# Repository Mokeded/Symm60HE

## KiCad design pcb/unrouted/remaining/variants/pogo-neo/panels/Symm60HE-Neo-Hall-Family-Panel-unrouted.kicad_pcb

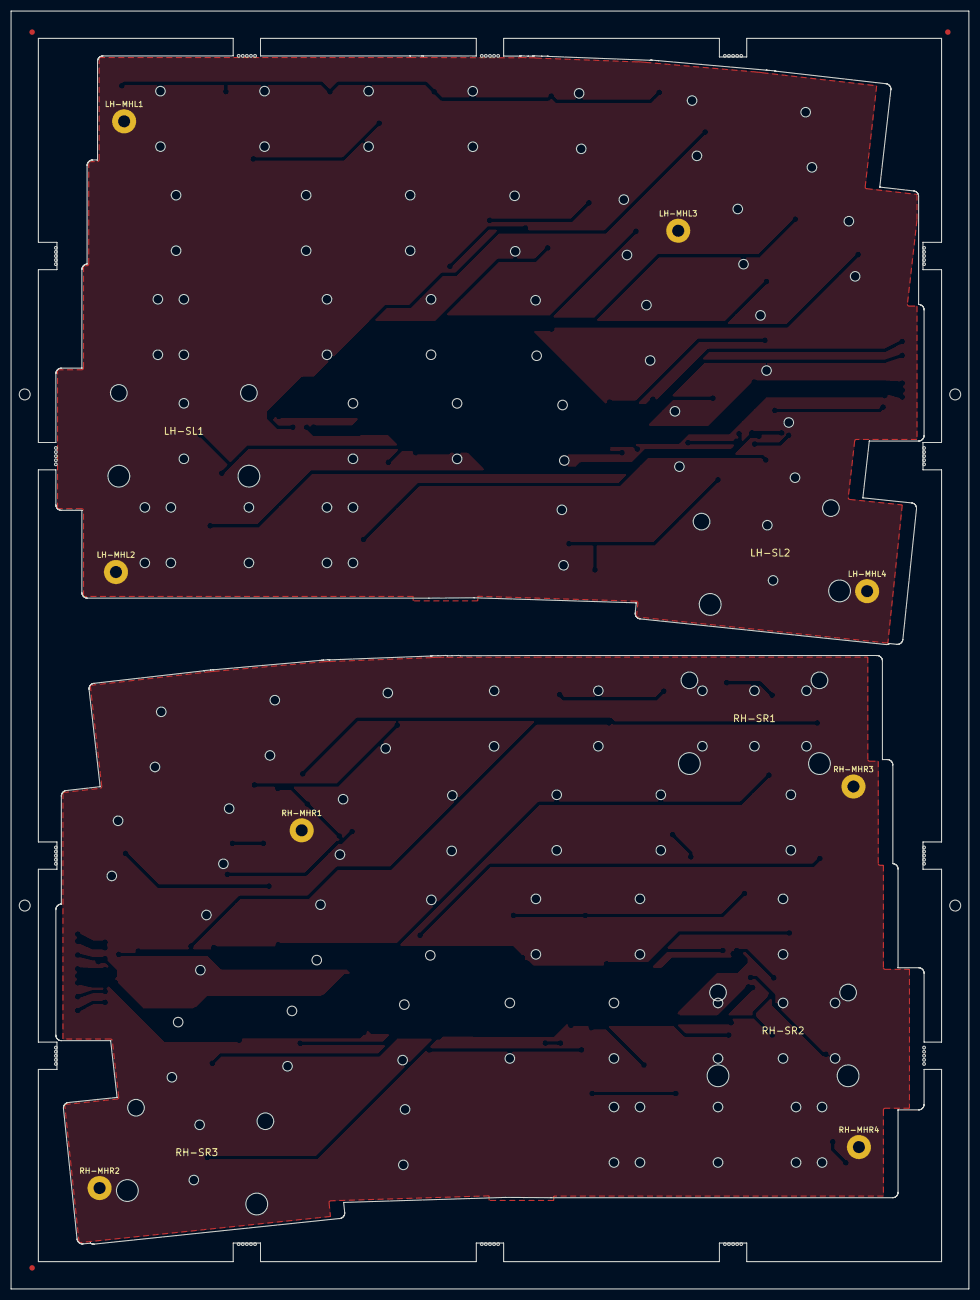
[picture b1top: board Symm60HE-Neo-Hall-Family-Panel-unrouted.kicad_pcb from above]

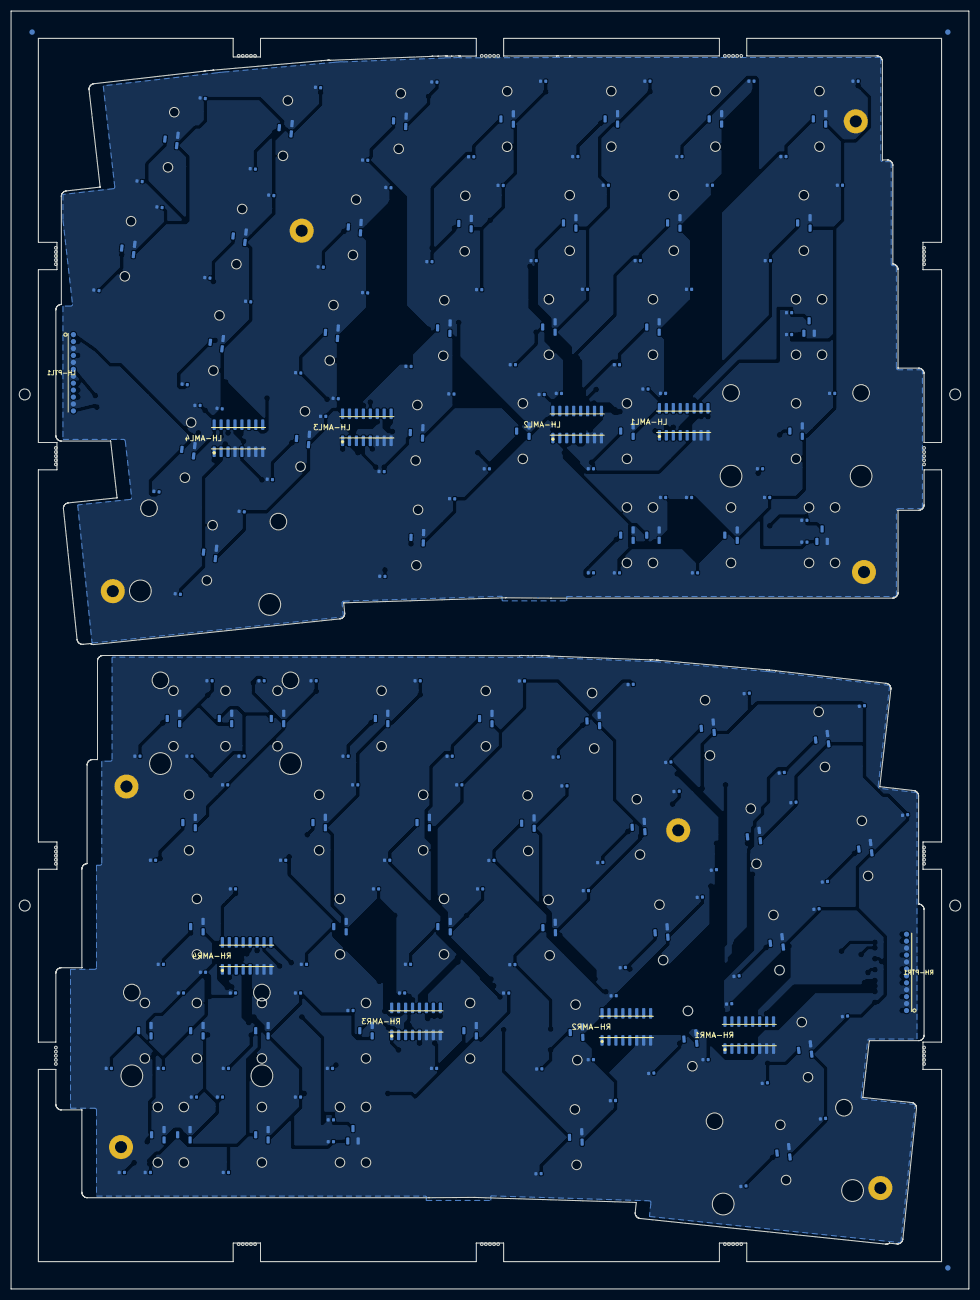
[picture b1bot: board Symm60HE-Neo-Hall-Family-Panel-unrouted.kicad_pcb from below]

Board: 2 copper layers, 175.3 x 233.9 mm, 318 parts (228 on the bottom side), 81 nets, no tracks yet.

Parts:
FIDB1, FIDB2, FIDB3: FIDUCIAL_1MM_BCU; Fiducial_1mm_BCu
FIDF1, FIDF2, FIDF3: FIDUCIAL_1MM_FCU; Fiducial_1mm_FCu
LH-AML1, LH-AML2, LH-AML3, LH-AML4: SN74LV4051A; AM1_SOIC-16_3.9x9.9mm_P1.27mm
LH-CL1A, LH-CL2A, LH-CL3A, LH-CL4A, LH-CL5A, LH-CL6A, LH-CL7A, LH-CL8A, LH-CL9A, LH-CL10A, LH-CL11A, LH-CL12A, LH-CL13A, LH-CL14A, LH-CL15A, LH-CL16A, LH-CL17A, LH-CL18A, LH-CL19A, LH-CL20A, LH-CL21A, LH-CL22A, LH-CL23A, LH-CL24A, LH-CL25A, LH-CL26A, LH-CL27A, LH-CL29A, LH-CL30A, LH-CL31A, LH-CL32A, LH-CL33A: 100n; C1_C_0402_1005Metric
LH-CL1B, LH-CL2B, LH-CL3B, LH-CL4B, LH-CL5B, LH-CL6B, LH-CL7B, LH-CL8B, LH-CL9B, LH-CL10B, LH-CL11B, LH-CL12B, LH-CL13B, LH-CL14B, LH-CL15B, LH-CL16B, LH-CL17B, LH-CL18B, LH-CL19B, LH-CL20B, LH-CL21B, LH-CL22B, LH-CL23B, LH-CL24B, LH-CL25B, LH-CL26B, LH-CL27B, LH-CL29B, LH-CL30B, LH-CL31B, LH-CL32B, LH-CL33B: 4.7n; C1_C_0402_1005Metric
LH-CML1, LH-CML2, LH-CML3, LH-CML4: 100n; C1_C_0402_1005Metric
LH-HEL1, LH-HEL2, LH-HEL3, LH-HEL4, LH-HEL5, LH-HEL6, LH-HEL7, LH-HEL9, LH-HEL10, LH-HEL11, LH-HEL12, LH-HEL13, LH-HEL14, LH-HEL16, LH-HEL17, LH-HEL18, LH-HEL19, LH-HEL20, LH-HEL22, LH-HEL23, LH-HEL24, LH-HEL25, LH-HEL26, LH-HEL29, LH-HEL31: MT9102ET; HE_KEY_1.00u
LH-HEL8, LH-HEL30, LH-HEL32: MT9102ET; HE_KEY_1.50u
LH-HEL15, LH-HEL27: MT9102ET; HE_SHARED_MIDPOINT
LH-HEL21, LH-HEL33: MT9102ET; HE_KEY_2.25u
LH-KML15N, LH-KML15S, LH-KML27A, LH-KML27N: MX_MECHANICAL_ONLY; HE_KEY_MECHANICAL_ONLY
LH-MHL1, LH-MHL2, LH-MHL3, LH-MHL4: M2; MountingHole_2.2mm_M2_Pad
LH-PTL1: 856-10-012-30-051000; MillMax_856-10-012-30-051000
LH-SL1, LH-SL2: STAB_MX; STABILIZER_MX_2U
MB1, MB2, MB3, MB4, MB5, MB6, MB7, MB8, MB9, MB10, MB11, MB12, MB13, MB14, MB15, MB16, MB17, MB18, MB19, MB20, MB21, MB22, MB23, MB24, MB25, MB26, MB27, MB28, MB29, MB30, MB31, MB32, MB33, MB34, MB35, MB36, MB37, MB38, MB39, MB40, MB41, MB42, MB43, MB44, MB45, MB46, MB47, MB48, MB49, MB50, MB51, MB52, MB53, MB54, MB55, MB56, MB57, MB58, MB59, MB60, MB61, MB62, MB63, MB64, MB65, MB66, MB67, MB68, MB69, MB70: MOUSE_BITE_0.5MM; MouseBite_0.5mm
RH-AMR1, RH-AMR2, RH-AMR3, RH-AMR4: SN74LV4051A; AM1_SOIC-16_3.9x9.9mm_P1.27mm
RH-CMR1, RH-CMR2, RH-CMR3, RH-CMR4: 100n; C1_C_0402_1005Metric
RH-CR1A, RH-CR2A, RH-CR3A, RH-CR4A, RH-CR5A, RH-CR6A, RH-CR7A, RH-CR8A, RH-CR9A, RH-CR10A, RH-CR11A, RH-CR12A, RH-CR13A, RH-CR14A, RH-CR15A, RH-CR16A, RH-CR17A, RH-CR18A, RH-CR19A, RH-CR20A, RH-CR21A, RH-CR22A, RH-CR23A, RH-CR24A, RH-CR25A, RH-CR26A, RH-CR27A, RH-CR28A, RH-CR29A, RH-CR30A, RH-CR32A, RH-CR33A, RH-CR34A, RH-CR35A, RH-CR36A: 100n; C1_C_0402_1005Metric
RH-CR1B, RH-CR2B, RH-CR3B, RH-CR4B, RH-CR5B, RH-CR6B, RH-CR7B, RH-CR8B, RH-CR9B, RH-CR10B, RH-CR11B, RH-CR12B, RH-CR13B, RH-CR14B, RH-CR15B, RH-CR16B, RH-CR17B, RH-CR18B, RH-CR19B, RH-CR20B, RH-CR21B, RH-CR22B, RH-CR23B, RH-CR24B, RH-CR25B, RH-CR26B, RH-CR27B, RH-CR28B, RH-CR29B, RH-CR30B, RH-CR32B, RH-CR33B, RH-CR34B, RH-CR35B, RH-CR36B: 4.7n; C1_C_0402_1005Metric
RH-HER1, RH-HER2, RH-HER3, RH-HER5, RH-HER6, RH-HER7, RH-HER8, RH-HER9, RH-HER10, RH-HER12, RH-HER13, RH-HER14, RH-HER15, RH-HER16, RH-HER17, RH-HER19, RH-HER20, RH-HER21, RH-HER22, RH-HER23, RH-HER24, RH-HER27, RH-HER28, RH-HER29, RH-HER32, RH-HER34: MT9102ET; HE_KEY_1.00u
RH-HER4: MT9102ET; HE_KEY_2.00u
RH-HER11, RH-HER33, RH-HER35: MT9102ET; HE_KEY_1.50u
RH-HER18: MT9102ET; HE_KEY_1.75u
RH-HER25, RH-HER36: MT9102ET; HE_KEY_2.25u
RH-HER26: MT9102ET; HE_KEY_1.25u
RH-HER30: MT9102ET; HE_SHARED_MIDPOINT
RH-KMR30A, RH-KMR30N: MX_MECHANICAL_ONLY; HE_KEY_MECHANICAL_ONLY
RH-MHR1, RH-MHR2, RH-MHR3, RH-MHR4: M2; MountingHole_2.2mm_M2_Pad
RH-PTR1: 856-10-012-30-051000; MillMax_856-10-012-30-051000
RH-SR1, RH-SR2, RH-SR3: STAB_MX; STABILIZER_MX_2U
TH1, TH2, TH3, TH4: TOOLING_HOLE_2MM; ToolingHole_2mm_NPTH

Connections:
/LH/+3V3A: LH-AML1.16, LH-AML2.16, LH-AML3.16, LH-AML4.16, LH-CL1A.1, LH-CL2A.1, LH-CL3A.1, LH-CL4A.1, LH-CL5A.1, LH-CL6A.1, LH-CL7A.1, LH-CL8A.1, LH-CL9A.1, LH-CL10A.1, LH-CL11A.1, LH-CL12A.1, LH-CL13A.1, LH-CL14A.1, LH-CL15A.1, LH-CL16A.1, LH-CL17A.1, LH-CL18A.1, LH-CL19A.1, LH-CL20A.1, LH-CL21A.1, LH-CL22A.1, LH-CL23A.1, LH-CL24A.1, LH-CL25A.1, LH-CL26A.1, LH-CL27A.1, LH-CL29A.1, LH-CL30A.1, LH-CL31A.1, LH-CL32A.1, LH-CL33A.1, LH-CML1.1, LH-CML2.1, LH-CML3.1, LH-CML4.1, LH-HEL1.1, LH-HEL2.1, LH-HEL3.1, LH-HEL4.1, LH-HEL5.1, LH-HEL6.1, LH-HEL7.1, LH-HEL8.1, LH-HEL9.1, LH-HEL10.1, LH-HEL11.1, LH-HEL12.1, LH-HEL13.1, LH-HEL14.1, LH-HEL15.1, LH-HEL16.1, LH-HEL17.1, LH-HEL18.1, LH-HEL19.1, LH-HEL20.1, LH-HEL21.1, LH-HEL22.1, LH-HEL23.1, LH-HEL24.1, LH-HEL25.1, LH-HEL26.1, LH-HEL27.1, LH-HEL29.1, LH-HEL30.1, LH-HEL31.1, LH-HEL32.1, LH-HEL33.1, LH-PTL1.12
/LH/ADC_L1: LH-AML1.3, LH-PTL1.6
/LH/ADC_L2: LH-AML2.3, LH-PTL1.4
/LH/ADC_L3: LH-AML3.3, LH-PTL1.2
/LH/ADC_L4: LH-AML4.3, LH-PTL1.1
/LH/GND: LH-AML1.6, LH-AML1.7, LH-AML1.8, LH-AML2.6, LH-AML2.7, LH-AML2.8, LH-AML3.6, LH-AML3.7, LH-AML3.8, LH-AML4.4, LH-AML4.6, LH-AML4.7, LH-AML4.8, LH-CL1A.2, LH-CL1B.2, LH-CL2A.2, LH-CL2B.2, LH-CL3A.2, LH-CL3B.2, LH-CL4A.2, LH-CL4B.2, LH-CL5A.2, LH-CL5B.2, LH-CL6A.2, LH-CL6B.2, LH-CL7A.2, LH-CL7B.2, LH-CL8A.2, LH-CL8B.2, LH-CL9A.2, LH-CL9B.2, LH-CL10A.2, LH-CL10B.2, LH-CL11A.2, LH-CL11B.2, LH-CL12A.2, LH-CL12B.2, LH-CL13A.2, LH-CL13B.2, LH-CL14A.2, LH-CL14B.2, LH-CL15A.2, LH-CL15B.2, LH-CL16A.2, LH-CL16B.2, LH-CL17A.2, LH-CL17B.2, LH-CL18A.2, LH-CL18B.2, LH-CL19A.2, LH-CL19B.2, LH-CL20A.2, LH-CL20B.2, LH-CL21A.2, LH-CL21B.2, LH-CL22A.2, LH-CL22B.2, LH-CL23A.2, LH-CL23B.2, LH-CL24A.2, LH-CL24B.2, LH-CL25A.2, LH-CL25B.2, LH-CL26A.2, LH-CL26B.2, LH-CL27A.2, LH-CL27B.2, LH-CL29A.2, LH-CL29B.2, LH-CL30A.2, LH-CL30B.2, LH-CL31A.2, LH-CL31B.2, LH-CL32A.2, LH-CL32B.2, LH-CL33A.2, LH-CL33B.2, LH-CML1.2, LH-CML2.2, LH-CML3.2, LH-CML4.2, LH-HEL1.2, LH-HEL2.2, LH-HEL3.2, LH-HEL4.2, LH-HEL5.2, LH-HEL6.2, LH-HEL7.2, LH-HEL8.2, LH-HEL9.2, LH-HEL10.2, LH-HEL11.2, LH-HEL12.2, LH-HEL13.2, LH-HEL14.2, LH-HEL15.2, LH-HEL16.2, LH-HEL17.2, LH-HEL18.2, LH-HEL19.2, LH-HEL20.2, LH-HEL21.2, LH-HEL22.2, LH-HEL23.2, LH-HEL24.2, LH-HEL25.2, LH-HEL26.2, LH-HEL27.2, LH-HEL29.2, LH-HEL30.2, LH-HEL31.2, LH-HEL32.2, LH-HEL33.2, LH-MHL1.1, LH-MHL2.1, LH-MHL3.1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
/LH/HE_L01: LH-AML1.13, LH-CL1B.1, LH-HEL1.3
/LH/HE_L02: LH-AML1.14, LH-CL2B.1, LH-HEL2.3
/LH/HE_L03: LH-AML1.15, LH-CL3B.1, LH-HEL3.3
/LH/HE_L04: LH-AML1.12, LH-CL4B.1, LH-HEL4.3
/LH/HE_L05: LH-AML1.1, LH-CL5B.1, LH-HEL5.3
/LH/HE_L06: LH-AML1.5, LH-CL6B.1, LH-HEL6.3
/LH/HE_L07: LH-AML1.2, LH-CL7B.1, LH-HEL7.3
/LH/HE_L08: LH-AML1.4, LH-CL8B.1, LH-HEL8.3
/LH/HE_L09: LH-AML2.13, LH-CL9B.1, LH-HEL9.3
/LH/HE_L10: LH-AML2.14, LH-CL10B.1, LH-HEL10.3
/LH/HE_L11: LH-AML2.15, LH-CL11B.1, LH-HEL11.3
/LH/HE_L12: LH-AML2.12, LH-CL12B.1, LH-HEL12.3
/LH/HE_L13: LH-AML2.1, LH-CL13B.1, LH-HEL13.3
/LH/HE_L14: LH-AML2.5, LH-CL14B.1, LH-HEL14.3
/LH/HE_L15: LH-AML2.2, LH-CL15B.1, LH-HEL15.3
/LH/HE_L16: LH-AML2.4, LH-CL16B.1, LH-HEL16.3
/LH/HE_L17: LH-AML3.13, LH-CL17B.1, LH-HEL17.3
/LH/HE_L18: LH-AML3.14, LH-CL18B.1, LH-HEL18.3
/LH/HE_L19: LH-AML3.15, LH-CL19B.1, LH-HEL19.3
/LH/HE_L20: LH-AML3.12, LH-CL20B.1, LH-HEL20.3
/LH/HE_L21: LH-AML3.1, LH-CL21B.1, LH-HEL21.3
/LH/HE_L22: LH-AML3.5, LH-CL22B.1, LH-HEL22.3
/LH/HE_L23: LH-AML3.2, LH-CL23B.1, LH-HEL23.3
/LH/HE_L24: LH-AML3.4, LH-CL24B.1, LH-HEL24.3
/LH/HE_L25: LH-AML4.13, LH-CL25B.1, LH-HEL25.3
/LH/HE_L26: LH-AML4.14, LH-CL26B.1, LH-HEL26.3
/LH/HE_L27: LH-AML4.15, LH-CL27B.1, LH-HEL27.3
/LH/HE_L28: LH-AML4.12, LH-CL29B.1, LH-CL30B.1, LH-HEL29.3, LH-HEL30.3
/LH/HE_L29: LH-AML4.1, LH-CL31B.1, LH-HEL31.3
/LH/HE_L30: LH-AML4.5, LH-CL32B.1, LH-HEL32.3
/LH/HE_L31: LH-AML4.2, LH-CL33B.1, LH-HEL33.3
/LH/MUX_A0: LH-AML1.11, LH-AML2.11, LH-AML3.11, LH-AML4.11, LH-PTL1.10
/LH/MUX_A1: LH-AML1.10, LH-AML2.10, LH-AML3.10, LH-AML4.10, LH-PTL1.9
/LH/MUX_A2: LH-AML1.9, LH-AML2.9, LH-AML3.9, LH-AML4.9, LH-PTL1.8
/RH/+3V3A: RH-AMR1.16, RH-AMR2.16, RH-AMR3.16, RH-AMR4.16, RH-CMR1.1, RH-CMR2.1, RH-CMR3.1, RH-CMR4.1, RH-CR1A.1, RH-CR2A.1, RH-CR3A.1, RH-CR4A.1, RH-CR5A.1, RH-CR6A.1, RH-CR7A.1, RH-CR8A.1, RH-CR9A.1, RH-CR10A.1, RH-CR11A.1, RH-CR12A.1, RH-CR13A.1, RH-CR14A.1, RH-CR15A.1, RH-CR16A.1, RH-CR17A.1, RH-CR18A.1, RH-CR19A.1, RH-CR20A.1, RH-CR21A.1, RH-CR22A.1, RH-CR23A.1, RH-CR24A.1, RH-CR25A.1, RH-CR26A.1, RH-CR27A.1, RH-CR28A.1, RH-CR29A.1, RH-CR30A.1, RH-CR32A.1, RH-CR33A.1, RH-CR34A.1, RH-CR35A.1, RH-CR36A.1, RH-HER1.1, RH-HER2.1, RH-HER3.1, RH-HER4.1, RH-HER5.1, RH-HER6.1, RH-HER7.1, RH-HER8.1, RH-HER9.1, RH-HER10.1, RH-HER11.1, RH-HER12.1, RH-HER13.1, RH-HER14.1, RH-HER15.1, RH-HER16.1, RH-HER17.1, RH-HER18.1, RH-HER19.1, RH-HER20.1, RH-HER21.1, RH-HER22.1, RH-HER23.1, RH-HER24.1, RH-HER25.1, RH-HER26.1, RH-HER27.1, RH-HER28.1, RH-HER29.1, RH-HER30.1, RH-HER32.1, RH-HER33.1, RH-HER34.1, RH-HER35.1, RH-HER36.1, RH-PTR1.1
/RH/ADC_R1: RH-AMR1.3, RH-PTR1.7
/RH/ADC_R2: RH-AMR2.3, RH-PTR1.9
/RH/ADC_R3: RH-AMR3.3, RH-PTR1.11
/RH/ADC_R4: RH-AMR4.3, RH-PTR1.12
/RH/GND: RH-AMR1.6, RH-AMR1.7, RH-AMR1.8, RH-AMR2.6, RH-AMR2.7, RH-AMR2.8, RH-AMR3.6, RH-AMR3.7, RH-AMR3.8, RH-AMR4.6, RH-AMR4.7, RH-AMR4.8, RH-CMR1.2, RH-CMR2.2, RH-CMR3.2, RH-CMR4.2, RH-CR1A.2, RH-CR1B.2, RH-CR2A.2, RH-CR2B.2, RH-CR3A.2, RH-CR3B.2, RH-CR4A.2, RH-CR4B.2, RH-CR5A.2, RH-CR5B.2, RH-CR6A.2, RH-CR6B.2, RH-CR7A.2, RH-CR7B.2, RH-CR8A.2, RH-CR8B.2, RH-CR9A.2, RH-CR9B.2, RH-CR10A.2, RH-CR10B.2, RH-CR11A.2, RH-CR11B.2, RH-CR12A.2, RH-CR12B.2, RH-CR13A.2, RH-CR13B.2, RH-CR14A.2, RH-CR14B.2, RH-CR15A.2, RH-CR15B.2, RH-CR16A.2, RH-CR16B.2, RH-CR17A.2, RH-CR17B.2, RH-CR18A.2, RH-CR18B.2, RH-CR19A.2, RH-CR19B.2, RH-CR20A.2, RH-CR20B.2, RH-CR21A.2, RH-CR21B.2, RH-CR22A.2, RH-CR22B.2, RH-CR23A.2, RH-CR23B.2, RH-CR24A.2, RH-CR24B.2, RH-CR25A.2, RH-CR25B.2, RH-CR26A.2, RH-CR26B.2, RH-CR27A.2, RH-CR27B.2, RH-CR28A.2, RH-CR28B.2, RH-CR29A.2, RH-CR29B.2, RH-CR30A.2, RH-CR30B.2, RH-CR32A.2, RH-CR32B.2, RH-CR33A.2, RH-CR33B.2, RH-CR34A.2, RH-CR34B.2, RH-CR35A.2, RH-CR35B.2, RH-CR36A.2, RH-CR36B.2, RH-HER1.2, RH-HER2.2, RH-HER3.2, RH-HER4.2, RH-HER5.2, RH-HER6.2, RH-HER7.2, RH-HER8.2, RH-HER9.2, RH-HER10.2, RH-HER11.2, RH-HER12.2, RH-HER13.2, RH-HER14.2, RH-HER15.2, RH-HER16.2, RH-HER17.2, RH-HER18.2, RH-HER19.2, RH-HER20.2, RH-HER21.2, RH-HER22.2, RH-HER23.2, RH-HER24.2, RH-HER25.2, RH-HER26.2, RH-HER27.2, RH-HER28.2, RH-HER29.2, RH-HER30.2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
/RH/HE_R01: RH-AMR1.13, RH-CR6B.1, RH-HER6.3
/RH/HE_R02: RH-AMR1.14, RH-CR1B.1, RH-HER1.3
/RH/HE_R03: RH-AMR1.15, RH-CR2B.1, RH-HER2.3
/RH/HE_R04: RH-AMR1.12, RH-CR3B.1, RH-CR4B.1, RH-HER3.3, RH-HER4.3
/RH/HE_R05: RH-AMR1.1, RH-CR5B.1, RH-HER5.3
/RH/HE_R06: RH-AMR1.5, RH-CR7B.1, RH-HER7.3
/RH/HE_R07: RH-AMR1.2, RH-CR8B.1, RH-HER8.3
/RH/HE_R08: RH-AMR1.4, RH-CR13B.1, RH-HER13.3
/RH/HE_R09: RH-AMR2.13, RH-CR12B.1, RH-HER12.3
/RH/HE_R10: RH-AMR2.14, RH-CR9B.1, RH-HER9.3
/RH/HE_R11: RH-AMR2.15, RH-CR10B.1, RH-HER10.3
/RH/HE_R12: RH-AMR2.12, RH-CR11B.1, RH-HER11.3
/RH/HE_R13: RH-AMR2.1, RH-CR14B.1, RH-HER14.3
/RH/HE_R14: RH-AMR2.5, RH-CR15B.1, RH-HER15.3
/RH/HE_R15: RH-AMR2.2, RH-CR19B.1, RH-HER19.3
/RH/HE_R16: RH-AMR2.4, RH-CR16B.1, RH-HER16.3
/RH/HE_R17: RH-AMR3.13, RH-CR17B.1, RH-HER17.3
/RH/HE_R18: RH-AMR3.14, RH-CR18B.1, RH-HER18.3
/RH/HE_R19: RH-AMR3.15, RH-CR20B.1, RH-HER20.3
/RH/HE_R20: RH-AMR3.12, RH-CR21B.1, RH-HER21.3
/RH/HE_R21: RH-AMR3.1, RH-CR27B.1, RH-HER27.3
/RH/HE_R22: RH-AMR3.5, RH-CR22B.1, RH-HER22.3
/RH/HE_R23: RH-AMR3.2, RH-CR23B.1, RH-HER23.3
/RH/HE_R24: RH-AMR3.4, RH-CR24B.1, RH-HER24.3
/RH/HE_R25: RH-AMR4.13, RH-CR25B.1, RH-CR26B.1, RH-HER25.3, RH-HER26.3
/RH/HE_R26: RH-AMR4.14, RH-CR28B.1, RH-HER28.3
/RH/HE_R27: RH-AMR4.15, RH-CR29B.1, RH-HER29.3
/RH/HE_R28: RH-AMR4.12, RH-CR35B.1, RH-HER35.3
/RH/HE_R29: RH-AMR4.1, RH-CR30B.1, RH-HER30.3
/RH/HE_R30: RH-AMR4.5, RH-CR32B.1, RH-CR33B.1, RH-HER32.3, RH-HER33.3
/RH/HE_R31: RH-AMR4.2, RH-CR34B.1, RH-HER34.3
/RH/HE_R32: RH-AMR4.4, RH-CR36B.1, RH-HER36.3
/RH/MUX_A0: RH-AMR1.11, RH-AMR2.11, RH-AMR3.11, RH-AMR4.11, RH-PTR1.3
/RH/MUX_A1: RH-AMR1.10, RH-AMR2.10, RH-AMR3.10, RH-AMR4.10, RH-PTR1.5
/RH/MUX_A2: RH-AMR1.9, RH-AMR2.9, RH-AMR3.9, RH-AMR4.9, RH-PTR1.6

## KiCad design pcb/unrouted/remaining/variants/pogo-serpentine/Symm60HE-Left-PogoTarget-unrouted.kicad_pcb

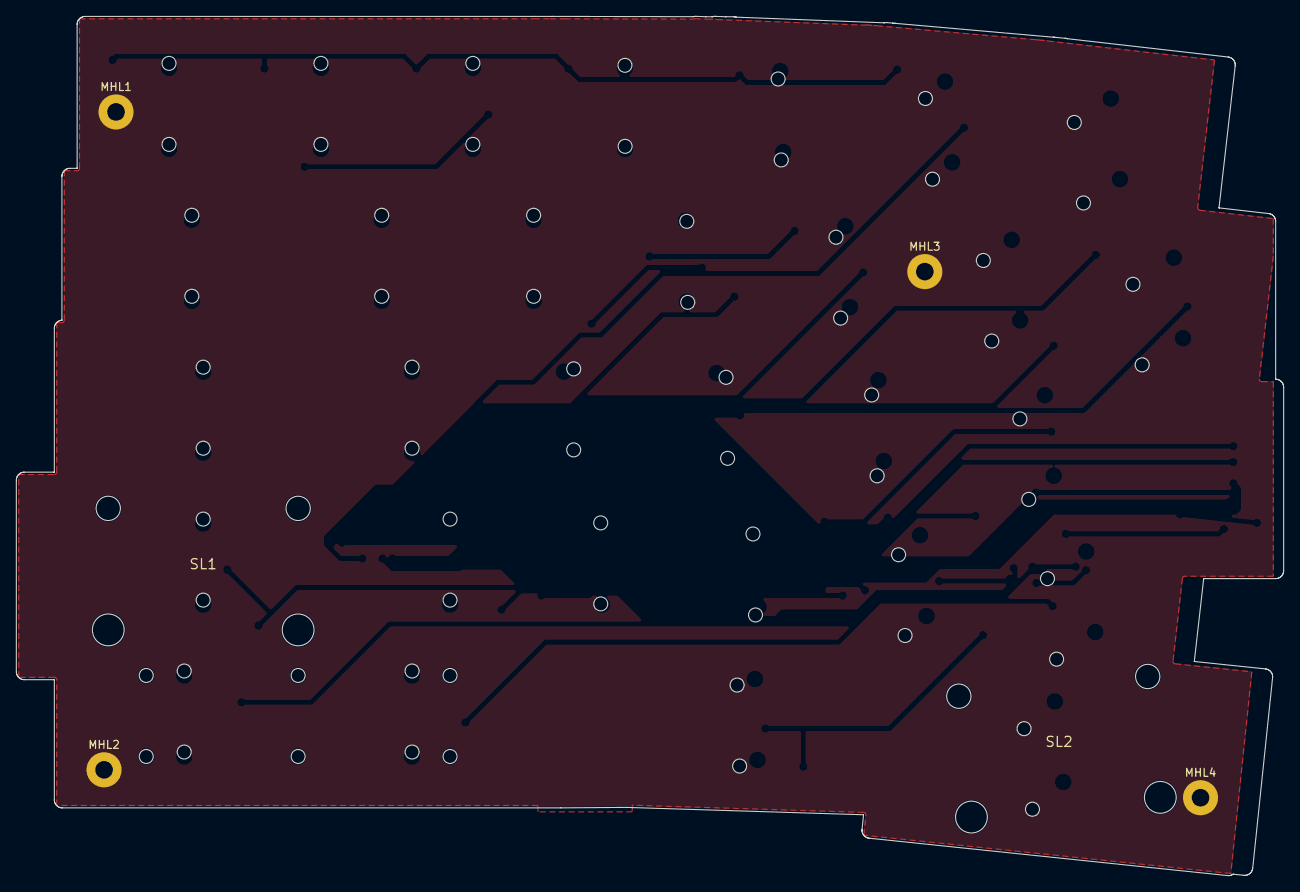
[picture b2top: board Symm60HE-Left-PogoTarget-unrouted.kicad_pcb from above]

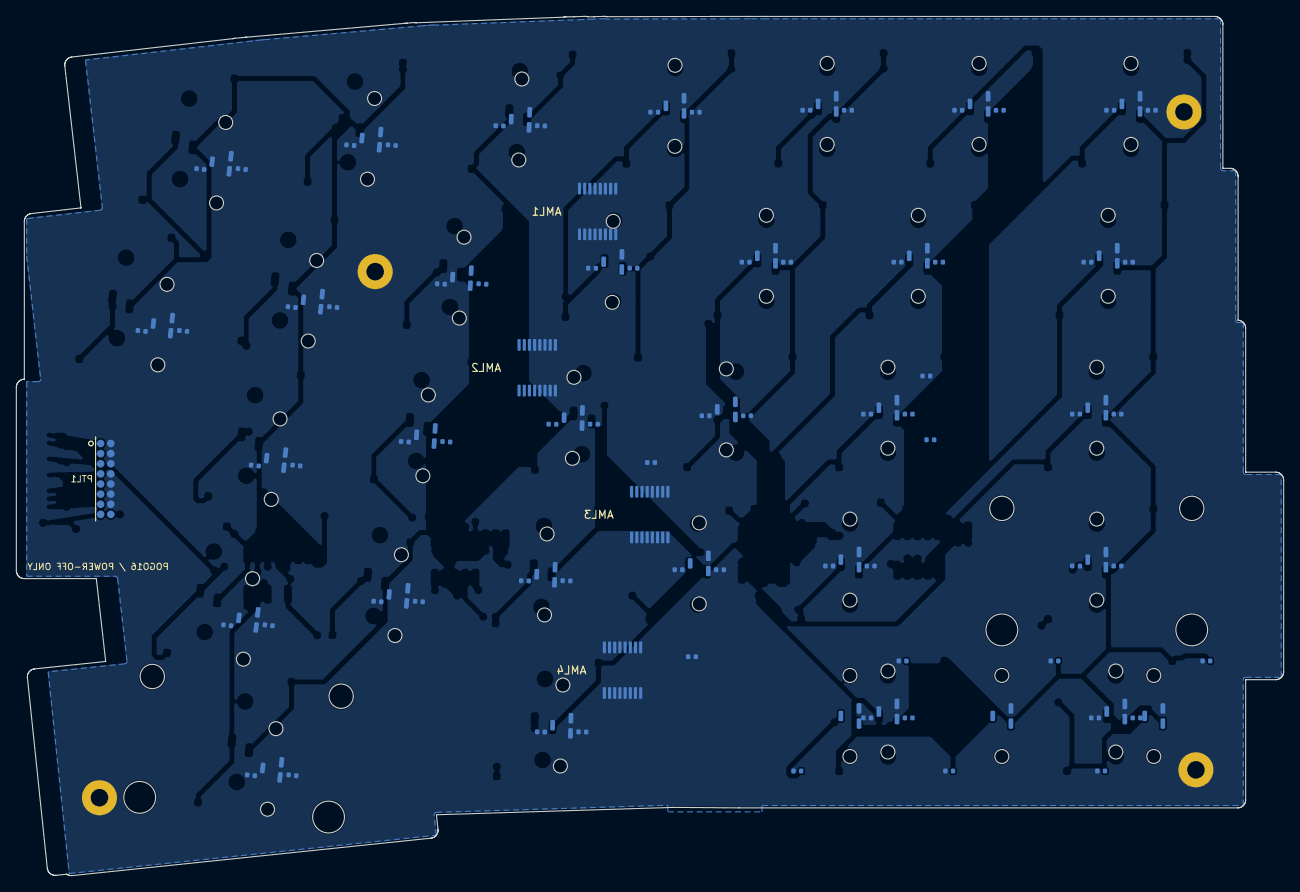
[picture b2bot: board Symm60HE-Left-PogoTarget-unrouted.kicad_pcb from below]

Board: 2 copper layers, 158.9 x 107.8 mm, 114 parts (108 on the bottom side), 40 nets, no tracks yet.

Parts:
AML1, AML2, AML3, AML4: SN74LV4051A; AM1_TSSOP-16_4.4x5mm_P0.65mm
CL1A, CL2A, CL3A, CL4A, CL5A, CL6A, CL7A, CL8A, CL9A, CL10A, CL11A, CL12A, CL13A, CL14A, CL15A, CL16A, CL17A, CL18A, CL19A, CL20A, CL21A, CL22A, CL23A, CL24A, CL25A, CL26A, CL27A, CL28A, CL29A, CL30A, CL31A, CL32A, CL33A: 100n; C1_C_0402_1005Metric
CL1B, CL2B, CL3B, CL4B, CL5B, CL6B, CL7B, CL8B, CL9B, CL10B, CL11B, CL12B, CL13B, CL14B, CL15B, CL16B, CL17B, CL18B, CL19B, CL20B, CL21B, CL22B, CL23B, CL24B, CL25B, CL26B, CL27B, CL28B, CL29B, CL30B, CL31B, CL32B, CL33B: 4.7n; C1_C_0402_1005Metric
CML1, CML2, CML3, CML4: 100n; C1_C_0402_1005Metric
HEL1, HEL2, HEL3, HEL4, HEL5, HEL6, HEL7, HEL9, HEL10, HEL11, HEL12, HEL13, HEL14, HEL16, HEL17, HEL18, HEL19, HEL20, HEL22, HEL23, HEL24, HEL25, HEL26, HEL27, HEL29, HEL31: MT9102ET; HE_KEY_1.00u
HEL8, HEL28, HEL30, HEL32: MT9102ET; HE_KEY_1.50u
HEL15: MT9102ET; HE_KEY_1.75u
HEL21, HEL33: MT9102ET; HE_KEY_2.25u
MHL1, MHL2, MHL3, MHL4: M2; MountingHole_2.2mm_M2_Pad
PTL1: 857-10-016-30-051000; MillMax_857-10-016-30-051000
SL1, SL2: STAB_MX; STABILIZER_MX_2U

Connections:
+3V3A: AML1.16, AML2.16, AML3.16, AML4.16, CL1A.1, CL2A.1, CL3A.1, CL4A.1, CL5A.1, CL6A.1, CL7A.1, CL8A.1, CL9A.1, CL10A.1, CL11A.1, CL12A.1, CL13A.1, CL14A.1, CL15A.1, CL16A.1, CL17A.1, CL18A.1, CL19A.1, CL20A.1, CL21A.1, CL22A.1, CL23A.1, CL24A.1, CL25A.1, CL26A.1, CL27A.1, CL28A.1, CL29A.1, CL30A.1, CL31A.1, CL32A.1, CL33A.1, CML1.1, CML2.1, CML3.1, CML4.1, HEL1.1, HEL2.1, HEL3.1, HEL4.1, HEL5.1, HEL6.1, HEL7.1, HEL8.1, HEL9.1, HEL10.1, HEL11.1, HEL12.1, HEL13.1, HEL14.1, HEL15.1, HEL16.1, HEL17.1, HEL18.1, HEL19.1, HEL20.1, HEL21.1, HEL22.1, HEL23.1, HEL24.1, HEL25.1, HEL26.1, HEL27.1, HEL28.1, HEL29.1, HEL30.1, HEL31.1, HEL32.1, HEL33.1, PTL1.15, PTL1.16
ADC_L1: AML1.3, PTL1.7
ADC_L2: AML2.3, PTL1.5
ADC_L3: AML3.3, PTL1.3
ADC_L4: AML4.3, PTL1.1
GND: AML1.6, AML1.7, AML1.8, AML2.6, AML2.7, AML2.8, AML3.6, AML3.7, AML3.8, AML4.4, AML4.6, AML4.7, AML4.8, CL1A.2, CL1B.2, CL2A.2, CL2B.2, CL3A.2, CL3B.2, CL4A.2, CL4B.2, CL5A.2, CL5B.2, CL6A.2, CL6B.2, CL7A.2, CL7B.2, CL8A.2, CL8B.2, CL9A.2, CL9B.2, CL10A.2, CL10B.2, CL11A.2, CL11B.2, CL12A.2, CL12B.2, CL13A.2, CL13B.2, CL14A.2, CL14B.2, CL15A.2, CL15B.2, CL16A.2, CL16B.2, CL17A.2, CL17B.2, CL18A.2, CL18B.2, CL19A.2, CL19B.2, CL20A.2, CL20B.2, CL21A.2, CL21B.2, CL22A.2, CL22B.2, CL23A.2, CL23B.2, CL24A.2, CL24B.2, CL25A.2, CL25B.2, CL26A.2, CL26B.2, CL27A.2, CL27B.2, CL28A.2, CL28B.2, CL29A.2, CL29B.2, CL30A.2, CL30B.2, CL31A.2, CL31B.2, CL32A.2, CL32B.2, CL33A.2, CL33B.2, CML1.2, CML2.2, CML3.2, CML4.2, HEL1.2, HEL2.2, HEL3.2, HEL4.2, HEL5.2, HEL6.2, HEL7.2, HEL8.2, HEL9.2, HEL10.2, HEL11.2, HEL12.2, HEL13.2, HEL14.2, HEL15.2, HEL16.2, HEL17.2, HEL18.2, HEL19.2, HEL20.2, HEL21.2, HEL22.2, HEL23.2, HEL24.2, HEL25.2, HEL26.2, HEL27.2, HEL28.2, HEL29.2, HEL30.2, HEL31.2, HEL32.2, HEL33.2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
HE_L01: AML1.13, CL1B.1, HEL1.3
HE_L02: AML1.14, CL2B.1, HEL2.3
HE_L03: AML1.15, CL3B.1, HEL3.3
HE_L04: AML1.12, CL4B.1, HEL4.3
HE_L05: AML1.1, CL5B.1, HEL5.3
HE_L06: AML1.5, CL6B.1, HEL6.3
HE_L07: AML1.2, CL7B.1, HEL7.3
HE_L08: AML1.4, CL8B.1, HEL8.3
HE_L09: AML2.13, CL9B.1, HEL9.3
HE_L10: AML2.14, CL10B.1, HEL10.3
HE_L11: AML2.15, CL11B.1, HEL11.3
HE_L12: AML2.12, CL12B.1, HEL12.3
HE_L13: AML2.1, CL13B.1, HEL13.3
HE_L14: AML2.5, CL14B.1, HEL14.3
HE_L15: AML2.2, CL15B.1, HEL15.3
HE_L16: AML2.4, CL16B.1, HEL16.3
HE_L17: AML3.13, CL17B.1, HEL17.3
HE_L18: AML3.14, CL18B.1, HEL18.3
HE_L19: AML3.15, CL19B.1, HEL19.3
HE_L20: AML3.12, CL20B.1, HEL20.3
HE_L21: AML3.1, CL21B.1, HEL21.3
HE_L22: AML3.5, CL22B.1, HEL22.3
HE_L23: AML3.2, CL23B.1, HEL23.3
HE_L24: AML3.4, CL24B.1, HEL24.3
HE_L25: AML4.13, CL25B.1, HEL25.3
HE_L26: AML4.14, CL26B.1, HEL26.3
HE_L27: AML4.15, CL27B.1, CL28B.1, HEL27.3, HEL28.3
HE_L28: AML4.12, CL29B.1, CL30B.1, HEL29.3, HEL30.3
HE_L29: AML4.1, CL31B.1, HEL31.3
HE_L30: AML4.5, CL32B.1, HEL32.3
HE_L31: AML4.2, CL33B.1, HEL33.3
MUX_A0: AML1.11, AML2.11, AML3.11, AML4.11, PTL1.13
MUX_A1: AML1.10, AML2.10, AML3.10, AML4.10, PTL1.11
MUX_A2: AML1.9, AML2.9, AML3.9, AML4.9, PTL1.9

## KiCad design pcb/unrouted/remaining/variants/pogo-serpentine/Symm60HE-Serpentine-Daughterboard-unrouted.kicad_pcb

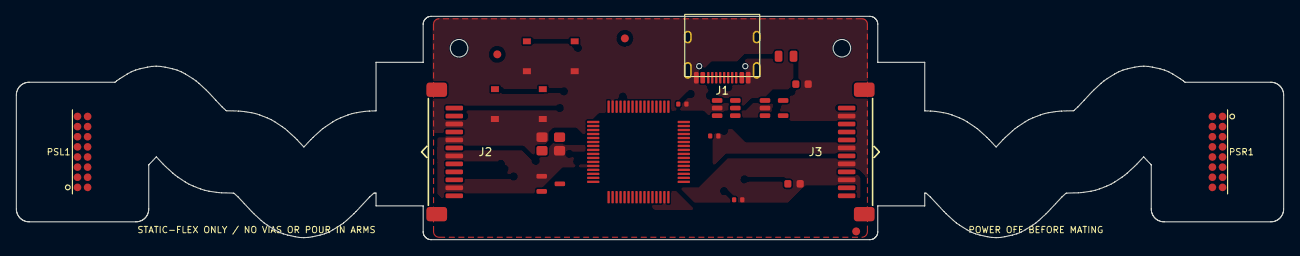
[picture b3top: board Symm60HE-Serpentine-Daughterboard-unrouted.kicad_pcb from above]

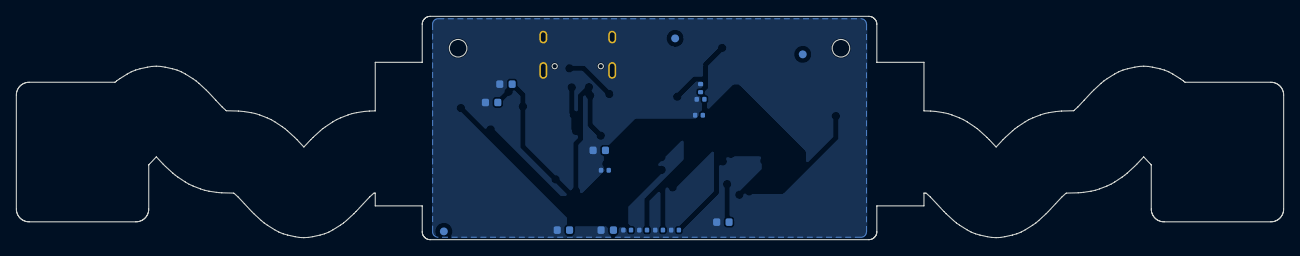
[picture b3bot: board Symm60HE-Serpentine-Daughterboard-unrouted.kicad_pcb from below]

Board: 2 copper layers, 158.9 x 28.0 mm, 40 parts (17 on the bottom side), 25 nets, no tracks yet.

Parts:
C1, C8: 10u; C148_C_0603_1608Metric
C2, C10: 1u; C148_C_0603_1608Metric
C3, C4: 30p; C1_C_0402_1005Metric
C5, C6, C7, C9, C11: 100n; C1_C_0402_1005Metric
C12, C13, C14, C15: 2.2u; C148_C_0603_1608Metric
F1: 0.5A; F1_Fuse_0805_2012Metric
FIDB1, FIDB2, FIDB3: FIDUCIAL_1MM_BCU; Fiducial_1mm_BCu
FIDF1, FIDF2, FIDF3: FIDUCIAL_1MM_FCU; Fiducial_1mm_FCu
J1: TYPE-C-31-M-12; USB_C_Receptacle_HRO_TYPE-C-31-M-12
J2, J3: DNP_TRANSITION_LANDS
MHD1, MHD2: M2_NPTH; MountingHole_2.2mm_M2_NPTH
PSL1: 855-22-016-30-004101; MillMax_855-22-016-30-004101
PSR1: 855-22-016-30-004101; MillMax_855-22-016-30-004101
R1, R4: 12k; R3_R_0402_1005Metric
R2, R3: 5.1k; R3_R_0402_1005Metric
SW1, SW2: TS-1187A; SW1_SW_Push_1P1T_XKB_TS-1187A
U1: AT32F405RCT7; U4_LQFP-64_10x10mm_P0.5mm
U2: USBLC6-2SC6; U1_SOT-23-6
U3: TLV75733PDBV; U2_SOT-23-5
U4: XC6206P332MR; U3_SOT-23-3
Y1: 12MHz; Y1_Crystal_SMD_3225-4Pin_3.2x2.5mm

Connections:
+3V3A: C9.1, C10.1, C15.1, J2.12, J3.12, PSL1.1, PSL1.2, PSR1.1, PSR1.2, U1.13, U4.2
+3V3D: C2.1, C5.1, C6.1, C7.1, C8.1, C13.1, C14.1, U1.1, U1.36, U1.64, U3.5, U4.3
ADC_L1: J2.6, PSL1.10, U1.17
ADC_L2: J2.4, PSL1.11, U1.20
ADC_L3: J2.2, PSL1.16, U1.21
ADC_L4: J2.1, PSL1.15, U1.22
ADC_R1: J3.6, PSR1.10, U1.23
ADC_R2: J3.4, PSR1.11, U1.24
ADC_R3: J3.2, PSR1.16, U1.25
ADC_R4: J3.1, PSR1.15, U1.26
BOOT0: R4.1, SW1.1, U1.60
CC1: J1.A5, R2.1
CC2: J1.B5, R3.1
GND: C1.2, C2.2, C3.2, C4.2, C5.2, C6.2, C7.2, C8.2, C9.2, C10.2, C11.2, C12.2, C13.2, C14.2, C15.2, J1.A1, J1.A12, J1.B1, J1.B12, J1.SH, J2.3, J2.5, J2.7, J2.11, J3.3, J3.5, J3.7, J3.11, PSL1.4, PSL1.7, PSL1.8, PSL1.9, PSL1.12, PSL1.13, PSL1.14, PSR1.4, PSR1.7, PSR1.8, PSR1.9, PSR1.12, PSR1.13, PSR1.14, R1.2, R2.2, R3.2, R4.2, SW1.2, SW2.2, U1.12, U1.31, U1.63, U2.2, U3.2, U4.1, Y1.2, Y1.4
MUX_A0: J2.10, J3.10, PSL1.3, PSR1.3, U1.9
MUX_A1: J2.9, J3.9, PSL1.6, PSR1.6, U1.10
MUX_A2: J2.8, J3.8, PSL1.5, PSR1.5, U1.11
NRST: C11.1, SW2.1, U1.7
USB_DM: J1.A7, J1.B7, U1.34, U2.3, U2.4
USB_DP: J1.A6, J1.B6, U1.35, U2.1, U2.6
USB_R: R1.1, U1.33
VBUS: C1.1, C12.1, F1.2, U2.5, U3.1
VBUS_IN: F1.1, J1.A4, J1.A9, J1.B4, J1.B9
XTAL_IN: C3.1, U1.5, Y1.1
XTAL_OUT: C4.1, U1.6, Y1.3

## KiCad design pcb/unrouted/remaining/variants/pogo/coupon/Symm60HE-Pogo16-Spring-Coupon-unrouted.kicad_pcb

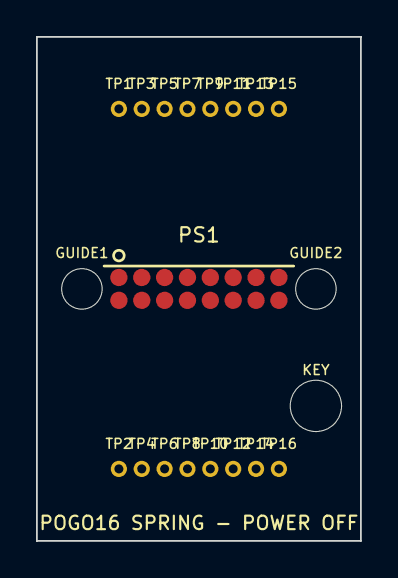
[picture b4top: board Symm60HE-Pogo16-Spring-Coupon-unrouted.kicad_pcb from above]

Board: 2 copper layers, 18.0 x 28.0 mm, 20 parts (0 on the bottom side), 16 nets, no tracks yet.

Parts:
GUIDE1: ALIGNMENT; GUIDE1
GUIDE2: ALIGNMENT; GUIDE2
KEY: ALIGNMENT; KEY
PS1: 855-22-016-30-004101; MillMax_855-22-016-30-004101
TP1, TP3, TP5, TP7, TP9, TP11, TP15: GND; THTPad_1.5x1.5mm_Drill0.8mm
TP2, TP4: +3V3A; THTPad_1.5x1.5mm_Drill0.8mm
TP6: MUX_A0; THTPad_1.5x1.5mm_Drill0.8mm
TP8: MUX_A1; THTPad_1.5x1.5mm_Drill0.8mm
TP10: MUX_A2; THTPad_1.5x1.5mm_Drill0.8mm
TP12: ADC_1; THTPad_1.5x1.5mm_Drill0.8mm
TP13: ADC_2; THTPad_1.5x1.5mm_Drill0.8mm
TP14: ADC_3; THTPad_1.5x1.5mm_Drill0.8mm
TP16: ADC_4; THTPad_1.5x1.5mm_Drill0.8mm

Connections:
P01: PS1.1, TP1.1
P02: PS1.2, TP2.1
P03: PS1.3, TP3.1
P04: PS1.4, TP4.1
P05: PS1.5, TP5.1
P06: PS1.6, TP6.1
P07: PS1.7, TP7.1
P08: PS1.8, TP8.1
P09: PS1.9, TP9.1
P10: PS1.10, TP10.1
P11: PS1.11, TP11.1
P12: PS1.12, TP12.1
P13: PS1.13, TP13.1
P14: PS1.14, TP14.1
P15: PS1.15, TP15.1
P16: PS1.16, TP16.1

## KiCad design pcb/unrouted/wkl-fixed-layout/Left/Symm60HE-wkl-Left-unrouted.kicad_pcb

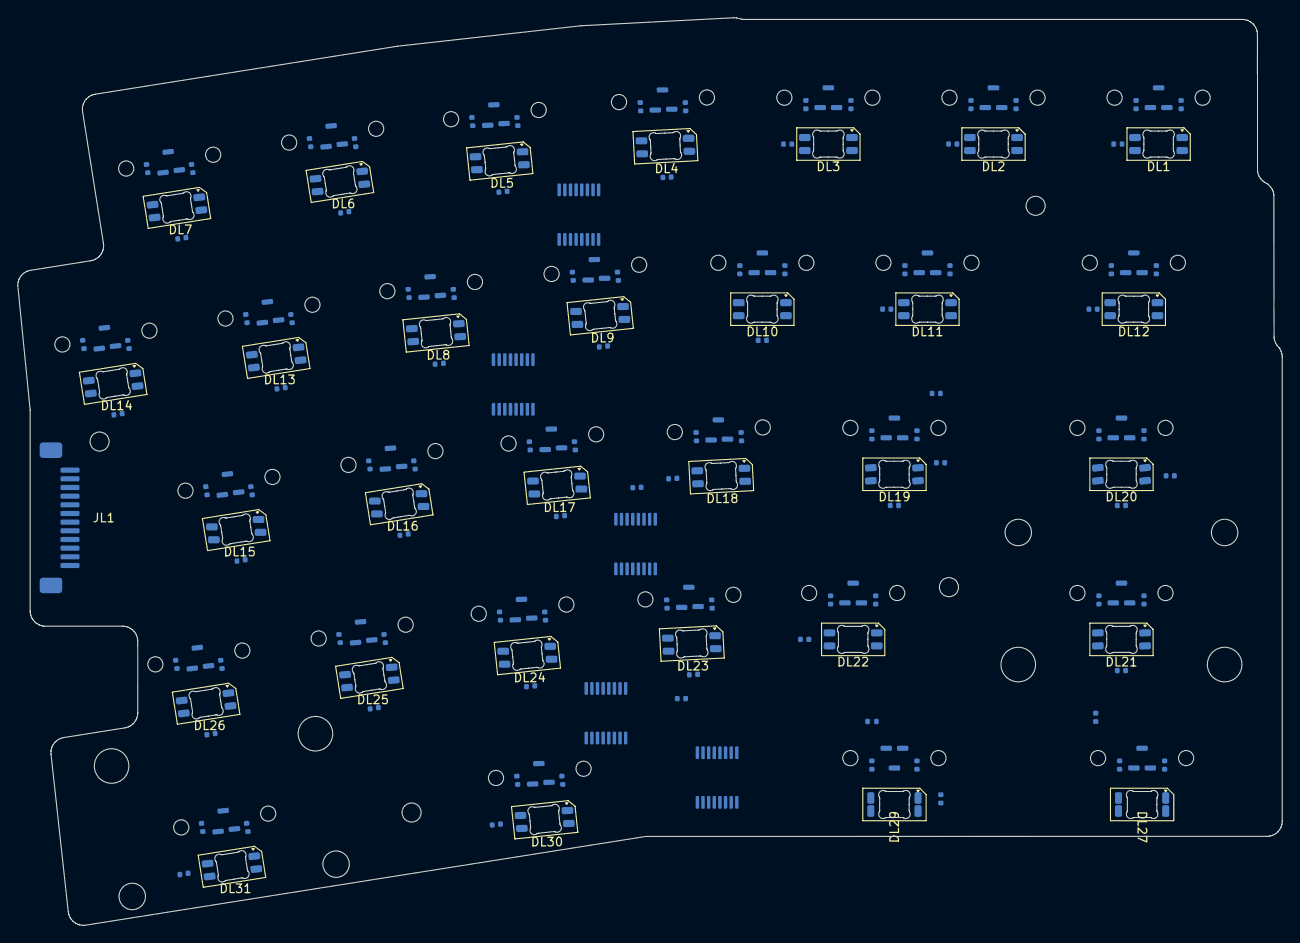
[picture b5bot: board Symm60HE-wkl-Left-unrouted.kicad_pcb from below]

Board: 2 copper layers, 145.9 x 104.7 mm, 168 parts (162 on the bottom side), 71 nets, no tracks yet.

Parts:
AML1, AML2, AML3, AML4, AML5: SN74LV4051A; AM1_TSSOP-16_4.4x5mm_P0.65mm
CL1A, CL2A, CL3A, CL4A, CL5A, CL6A, CL7A, CL8A, CL9A, CL10A, CL11A, CL12A, CL13A, CL14A, CL15A, CL16A, CL17A, CL18A, CL19A, CL20A, CL21A, CL22A, CL23A, CL24A, CL25A, CL26A, CL28A, CL30A, CL32A, CL33A: 100n; C1_C_0402_1005Metric
CL1B, CL2B, CL3B, CL4B, CL5B, CL6B, CL7B, CL8B, CL9B, CL10B, CL11B, CL12B, CL13B, CL14B, CL15B, CL16B, CL17B, CL18B, CL19B, CL20B, CL21B, CL22B, CL23B, CL24B, CL25B, CL26B, CL28B, CL30B, CL32B, CL33B: 4.7n; C1_C_0402_1005Metric
CML1, CML2, CML3, CML4, CML5: 100n; C1_C_0402_1005Metric
CRGBL1, CRGBL2, CRGBL3, CRGBL4, CRGBL5, CRGBL6, CRGBL7, CRGBL8, CRGBL9, CRGBL10, CRGBL11, CRGBL12, CRGBL13, CRGBL14, CRGBL15, CRGBL16, CRGBL17, CRGBL18, CRGBL19, CRGBL20, CRGBL21, CRGBL22, CRGBL23, CRGBL24, CRGBL25, CRGBL26, CRGBL27, CRGBL29, CRGBL30, CRGBL31: 100n; C1_C_0402_1005Metric
DL1, DL2, DL3, DL4, DL5, DL6, DL7, DL8, DL9, DL10, DL11, DL12, DL13, DL14, DL15, DL16, DL17, DL18, DL19, DL20, DL21, DL22, DL23, DL24, DL25, DL26, DL27, DL29, DL30, DL31: SK6812MINI-E; SK6812MINI-E_ReverseMount
HEL1, HEL2, HEL3, HEL4, HEL5, HEL6, HEL7, HEL9, HEL10, HEL11, HEL12, HEL13, HEL14, HEL16, HEL17, HEL18, HEL19, HEL20, HEL22, HEL23, HEL24, HEL25, HEL26: MT9102ET; HE_KEY_1.00u
HEL8, HEL28, HEL30, HEL32: MT9102ET; HE_KEY_1.50u
HEL15: MT9102ET; HE_KEY_1.75u
HEL21, HEL33: MT9102ET; HE_KEY_2.25u
JL1: FFC_12P; FFC_12P_1.00mm_TopContact
MHL1, MHL2, MHL3, MHL4: M2_NPTH; MountingHole_2.2mm_M2_NPTH
RBPL29: 0R_DNP; R3_R_0402_1005Metric
SL1, SL2: STAB_MX; STABILIZER_MX_2U

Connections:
+3V3A: AML1.16, AML2.16, AML3.16, AML4.16, AML5.16, CL1A.1, CL2A.1, CL3A.1, CL4A.1, CL5A.1, CL6A.1, CL7A.1, CL8A.1, CL9A.1, CL10A.1, CL11A.1, CL12A.1, CL13A.1, CL14A.1, CL15A.1, CL16A.1, CL17A.1, CL18A.1, CL19A.1, CL20A.1, CL21A.1, CL22A.1, CL23A.1, CL24A.1, CL25A.1, CL26A.1, CL28A.1, CL30A.1, CL32A.1, CL33A.1, CML1.1, CML2.1, CML3.1, CML4.1, CML5.1, HEL1.1, HEL2.1, HEL3.1, HEL4.1, HEL5.1, HEL6.1, HEL7.1, HEL8.1, HEL9.1, HEL10.1, HEL11.1, HEL12.1, HEL13.1, HEL14.1, HEL15.1, HEL16.1, HEL17.1, HEL18.1, HEL19.1, HEL20.1, HEL21.1, HEL22.1, HEL23.1, HEL24.1, HEL25.1, HEL26.1, HEL28.1, HEL30.1, HEL32.1, HEL33.1, JL1.12
ADC_L1: AML1.3, JL1.1
ADC_L2: AML2.3, JL1.2
ADC_L3: AML3.3, JL1.4
ADC_L4: AML4.3, JL1.6
ADC_L5: AML5.3, JL1.11
GND: AML1.6, AML1.7, AML1.8, AML2.6, AML2.7, AML2.8, AML3.6, AML3.7, AML3.8, AML4.6, AML4.7, AML4.8, AML5.6, AML5.7, AML5.8, CL1A.2, CL1B.2, CL2A.2, CL2B.2, CL3A.2, CL3B.2, CL4A.2, CL4B.2, CL5A.2, CL5B.2, CL6A.2, CL6B.2, CL7A.2, CL7B.2, CL8A.2, CL8B.2, CL9A.2, CL9B.2, CL10A.2, CL10B.2, CL11A.2, CL11B.2, CL12A.2, CL12B.2, CL13A.2, CL13B.2, CL14A.2, CL14B.2, CL15A.2, CL15B.2, CL16A.2, CL16B.2, CL17A.2, CL17B.2, CL18A.2, CL18B.2, CL19A.2, CL19B.2, CL20A.2, CL20B.2, CL21A.2, CL21B.2, CL22A.2, CL22B.2, CL23A.2, CL23B.2, CL24A.2, CL24B.2, CL25A.2, CL25B.2, CL26A.2, CL26B.2, CL28A.2, CL28B.2, CL30A.2, CL30B.2, CL32A.2, CL32B.2, CL33A.2, CL33B.2, CML1.2, CML2.2, CML3.2, CML4.2, CML5.2, CRGBL1.2, CRGBL2.2, CRGBL3.2, CRGBL4.2, CRGBL5.2, CRGBL6.2, CRGBL7.2, CRGBL8.2, CRGBL9.2, CRGBL10.2, CRGBL11.2, CRGBL12.2, CRGBL13.2, CRGBL14.2, CRGBL15.2, CRGBL16.2, CRGBL17.2, CRGBL18.2, CRGBL19.2, CRGBL20.2, CRGBL21.2, CRGBL22.2, CRGBL23.2, CRGBL24.2, CRGBL25.2, CRGBL26.2, CRGBL27.2, CRGBL29.2, CRGBL30.2, CRGBL31.2, DL1.1, DL2.1, DL3.1, DL4.1, DL5.1, DL6.1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
HE_L01: AML1.1, CL1B.1, HEL1.3
HE_L02: AML1.2, CL2B.1, HEL2.3
HE_L03: AML1.4, CL3B.1, HEL3.3
HE_L04: AML1.5, CL4B.1, HEL4.3
HE_L05: AML1.15, CL5B.1, HEL5.3
HE_L06: AML1.14, CL6B.1, HEL6.3
HE_L07: AML1.13, CL7B.1, HEL7.3
HE_L08: AML2.1, CL8B.1, HEL8.3
HE_L09: AML2.2, CL9B.1, HEL9.3
HE_L10: AML2.4, CL10B.1, HEL10.3
HE_L11: AML2.5, CL11B.1, HEL11.3
HE_L12: AML2.15, CL12B.1, HEL12.3
HE_L13: AML2.14, CL13B.1, HEL13.3
HE_L14: AML2.13, CL14B.1, HEL14.3
HE_L15: AML3.1, CL15B.1, HEL15.3
HE_L16: AML3.2, CL16B.1, HEL16.3
HE_L17: AML3.4, CL17B.1, HEL17.3
HE_L18: AML3.15, CL18B.1, HEL18.3
HE_L19: AML3.14, CL19B.1, HEL19.3
HE_L20: AML3.13, CL20B.1, HEL20.3
HE_L21: AML4.1, CL21B.1, HEL21.3
HE_L22: AML4.2, CL22B.1, HEL22.3
HE_L23: AML4.4, CL23B.1, HEL23.3
HE_L24: AML4.15, CL24B.1, HEL24.3
HE_L25: AML4.14, CL25B.1, HEL25.3
HE_L26: AML4.13, CL26B.1, HEL26.3
HE_L30: AML5.15, CL32B.1, HEL32.3
HE_L31: AML5.14, CL33B.1, HEL33.3
HE_L32: AML5.1, CL28B.1, HEL28.3
HE_L33: AML5.2, CL30B.1, HEL30.3
MUX_A0: AML1.11, AML2.11, AML3.11, AML4.11, AML5.11, JL1.10
MUX_A1: AML1.10, AML2.10, AML3.10, AML4.10, AML5.10, JL1.9
MUX_A2: AML1.9, AML2.9, AML3.9, AML4.9, AML5.9, JL1.8
RGB_L: DL1.2, JL1.3
RGB_L_01: DL1.4, DL2.2
RGB_L_02: DL2.4, DL3.2
RGB_L_03: DL3.4, DL4.2
RGB_L_04: DL4.4, DL5.2
RGB_L_05: DL5.4, DL6.2
RGB_L_06: DL6.4, DL7.2
RGB_L_07: DL7.4, DL8.2
RGB_L_08: DL8.4, DL9.2
RGB_L_09: DL9.4, DL10.2
RGB_L_10: DL10.4, DL11.2
RGB_L_11: DL11.4, DL12.2
RGB_L_12: DL12.4, DL13.2
RGB_L_13: DL13.4, DL14.2
RGB_L_14: DL14.4, DL15.2
RGB_L_15: DL15.4, DL16.2
RGB_L_16: DL16.4, DL17.2
RGB_L_17: DL17.4, DL18.2
RGB_L_18: DL18.4, DL19.2
RGB_L_19: DL19.4, DL20.2
RGB_L_20: DL20.4, DL21.2
RGB_L_21: DL21.4, DL22.2
RGB_L_22: DL22.4, DL23.2
RGB_L_23: DL23.4, DL24.2
RGB_L_24: DL24.4, DL25.2
RGB_L_25: DL25.4, DL26.2
RGB_L_26: DL26.4, DL27.2
RGB_L_27: DL27.4, DL29.2, RBPL29.1
RGB_L_29: DL29.4, DL30.2, RBPL29.2
RGB_L_30: DL30.4, DL31.2
VBUS: CRGBL1.1, CRGBL2.1, CRGBL3.1, CRGBL4.1, CRGBL5.1, CRGBL6.1, CRGBL7.1, CRGBL8.1, CRGBL9.1, CRGBL10.1, CRGBL11.1, CRGBL12.1, CRGBL13.1, CRGBL14.1, CRGBL15.1, CRGBL16.1, CRGBL17.1, CRGBL18.1, CRGBL19.1, CRGBL20.1, CRGBL21.1, CRGBL22.1, CRGBL23.1, CRGBL24.1, CRGBL25.1, CRGBL26.1, CRGBL27.1, CRGBL29.1, CRGBL30.1, CRGBL31.1, DL1.3, DL2.3, DL3.3, DL4.3, DL5.3, DL6.3, DL7.3, DL8.3, DL9.3, DL10.3, DL11.3, DL12.3, DL13.3, DL14.3, DL15.3, DL16.3, DL17.3, DL18.3, DL19.3, DL20.3, DL21.3, DL22.3, DL23.3, DL24.3, DL25.3, DL26.3, DL27.3, DL29.3, DL30.3, DL31.3, JL1.7
